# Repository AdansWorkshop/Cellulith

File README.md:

# Cellulith
An RP2040 based IoT/cellular device. Essentially a cell phone but very bulky.

# Why it's called "Cellulith"
Lith means rock or stone. For example, the Earths crust is called the lithosphere because it's a sphere of rock.

Cellu comes from cellular, like cellular phone.

The inspiration for the name was Cellulite, which was proposed by the founder of Oak Dev Tech, however I felt that the "lite" suffix made it sound small.

# Specifications
2aH Li-Po battery with USB-C charging

SIM808 GSM/GPS module with sim card socket on the bottom of the board (sim card not included)

RP2040 Cortex M0+ high-performance microcontroller running at 133MHz

8MB QSPI NOR FLASH storage

320x480 Resistive Touchscreen TFT-LCD Display

Himax HM01B0 CMOS Color Imaging Camera

Digital PWM Audio

Haptic Feedback for SMS/Voice Call notifications

# Board Dimensions
3.8" by 2.6" with M3 mounting holes in all 4 corners

# Case Dimensions
4.2" by 3" by 0.95" excluding antenna

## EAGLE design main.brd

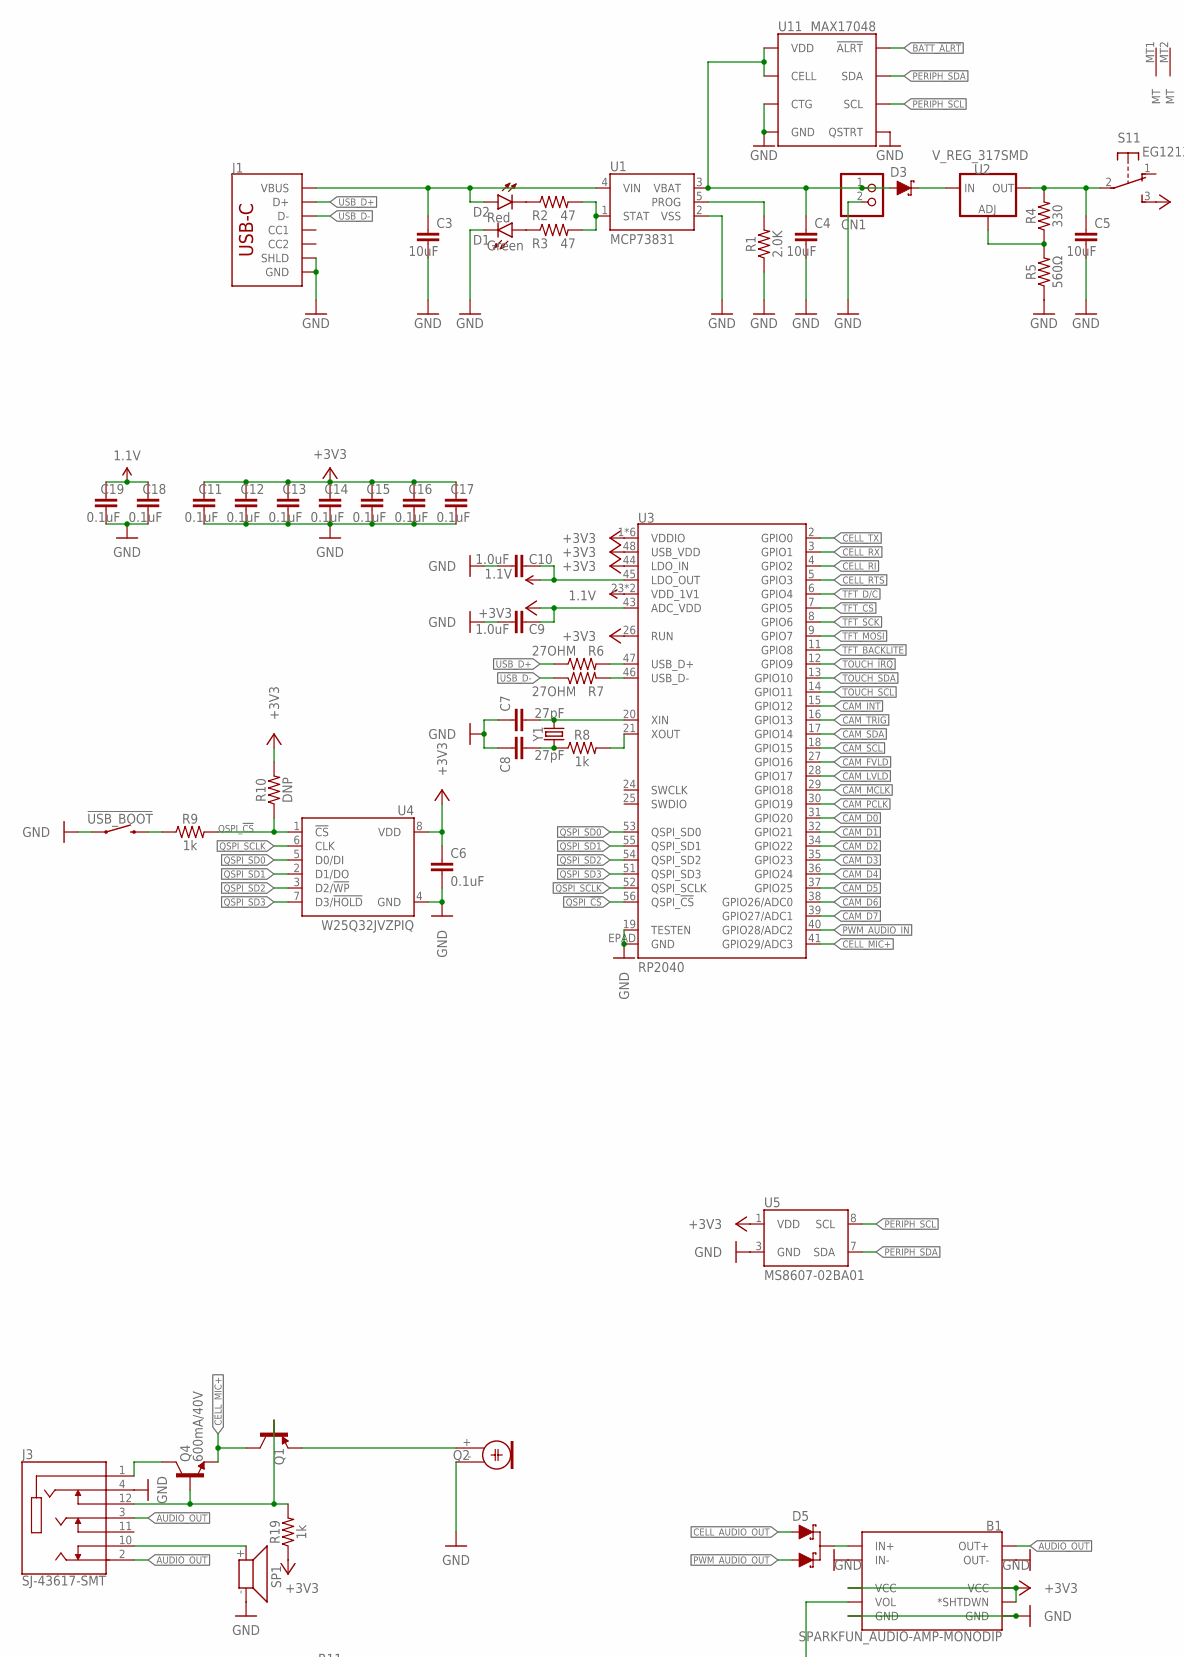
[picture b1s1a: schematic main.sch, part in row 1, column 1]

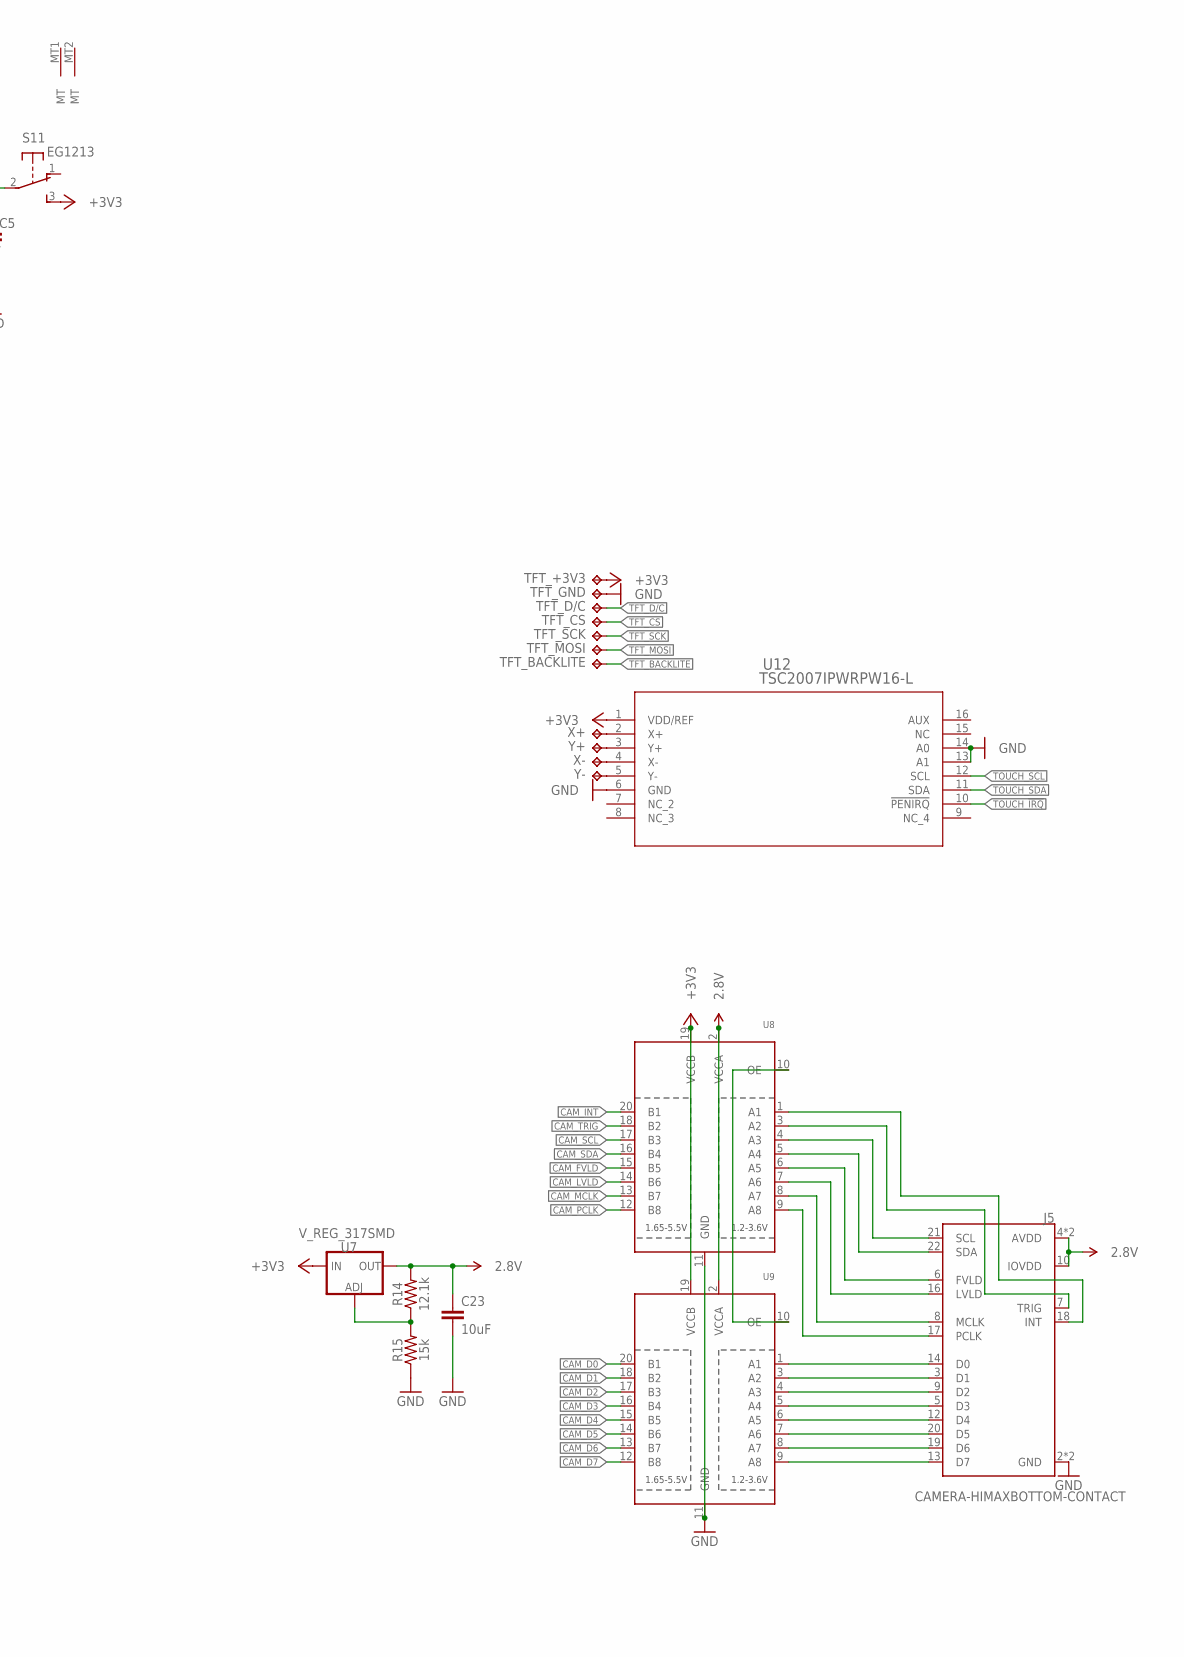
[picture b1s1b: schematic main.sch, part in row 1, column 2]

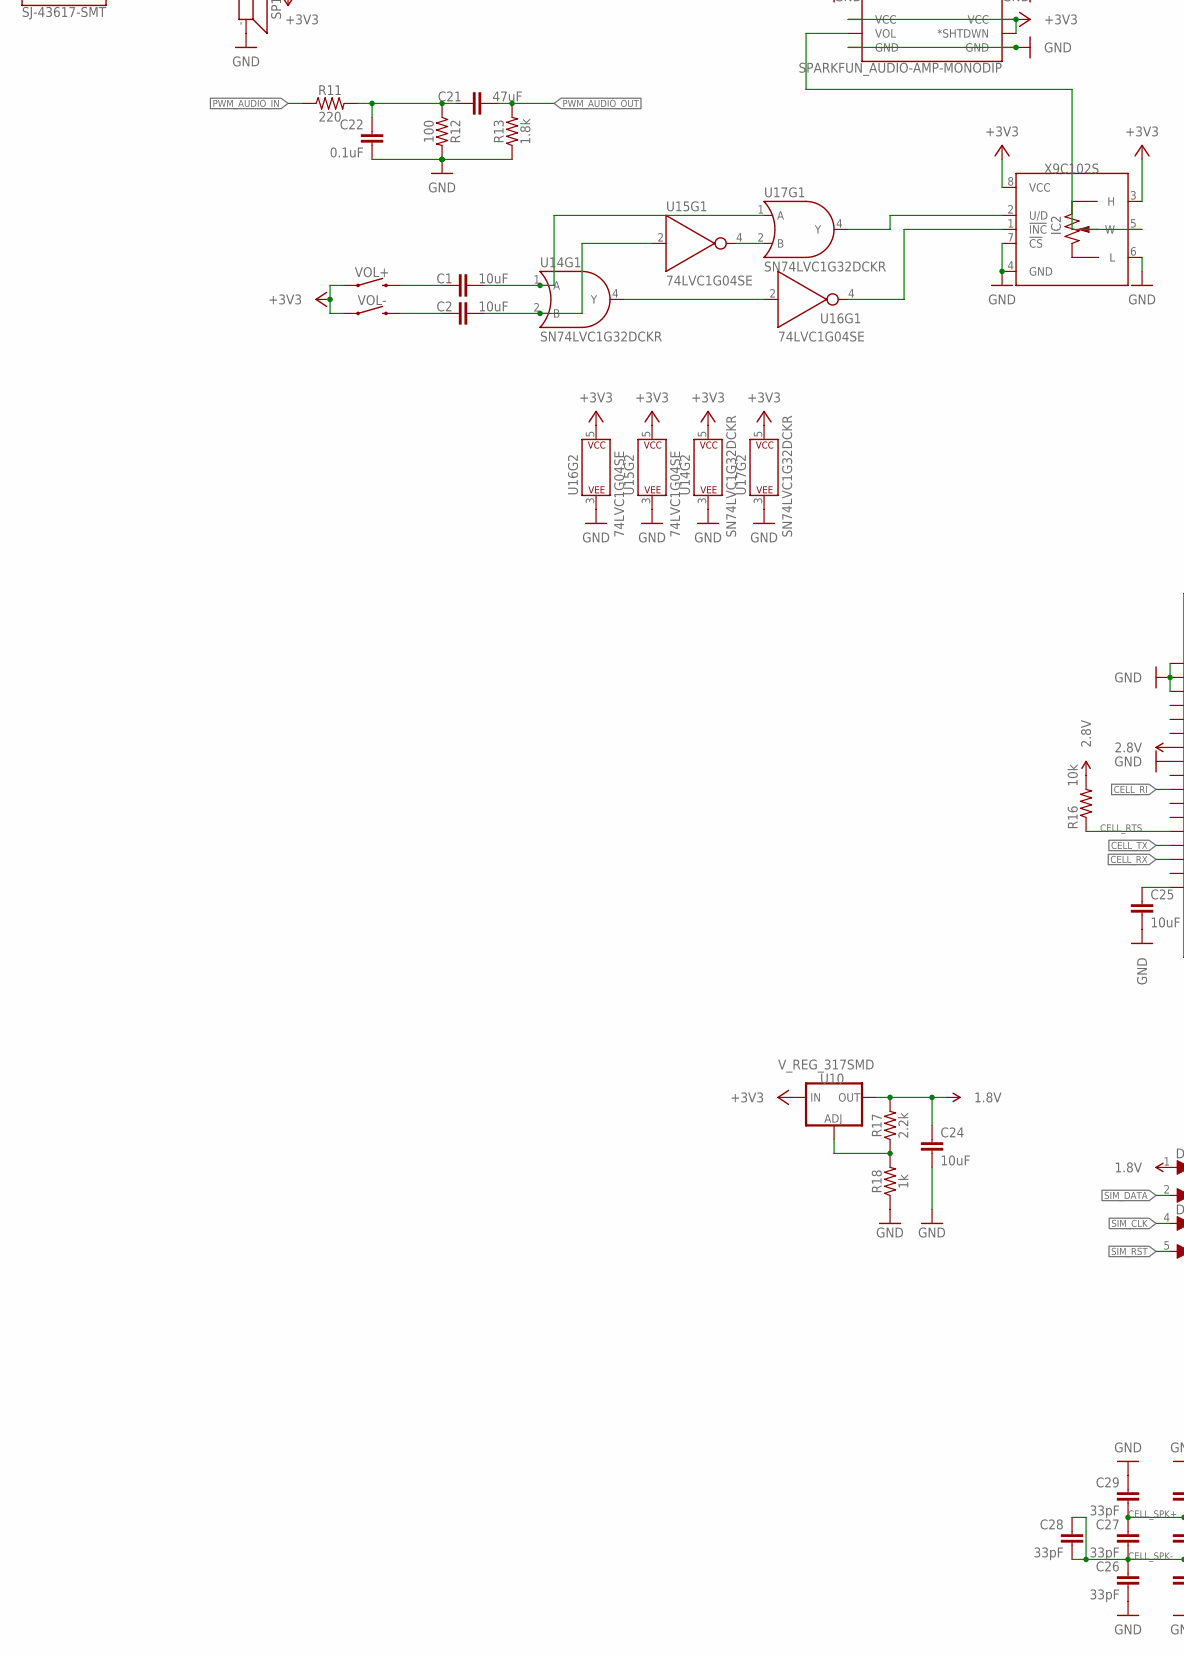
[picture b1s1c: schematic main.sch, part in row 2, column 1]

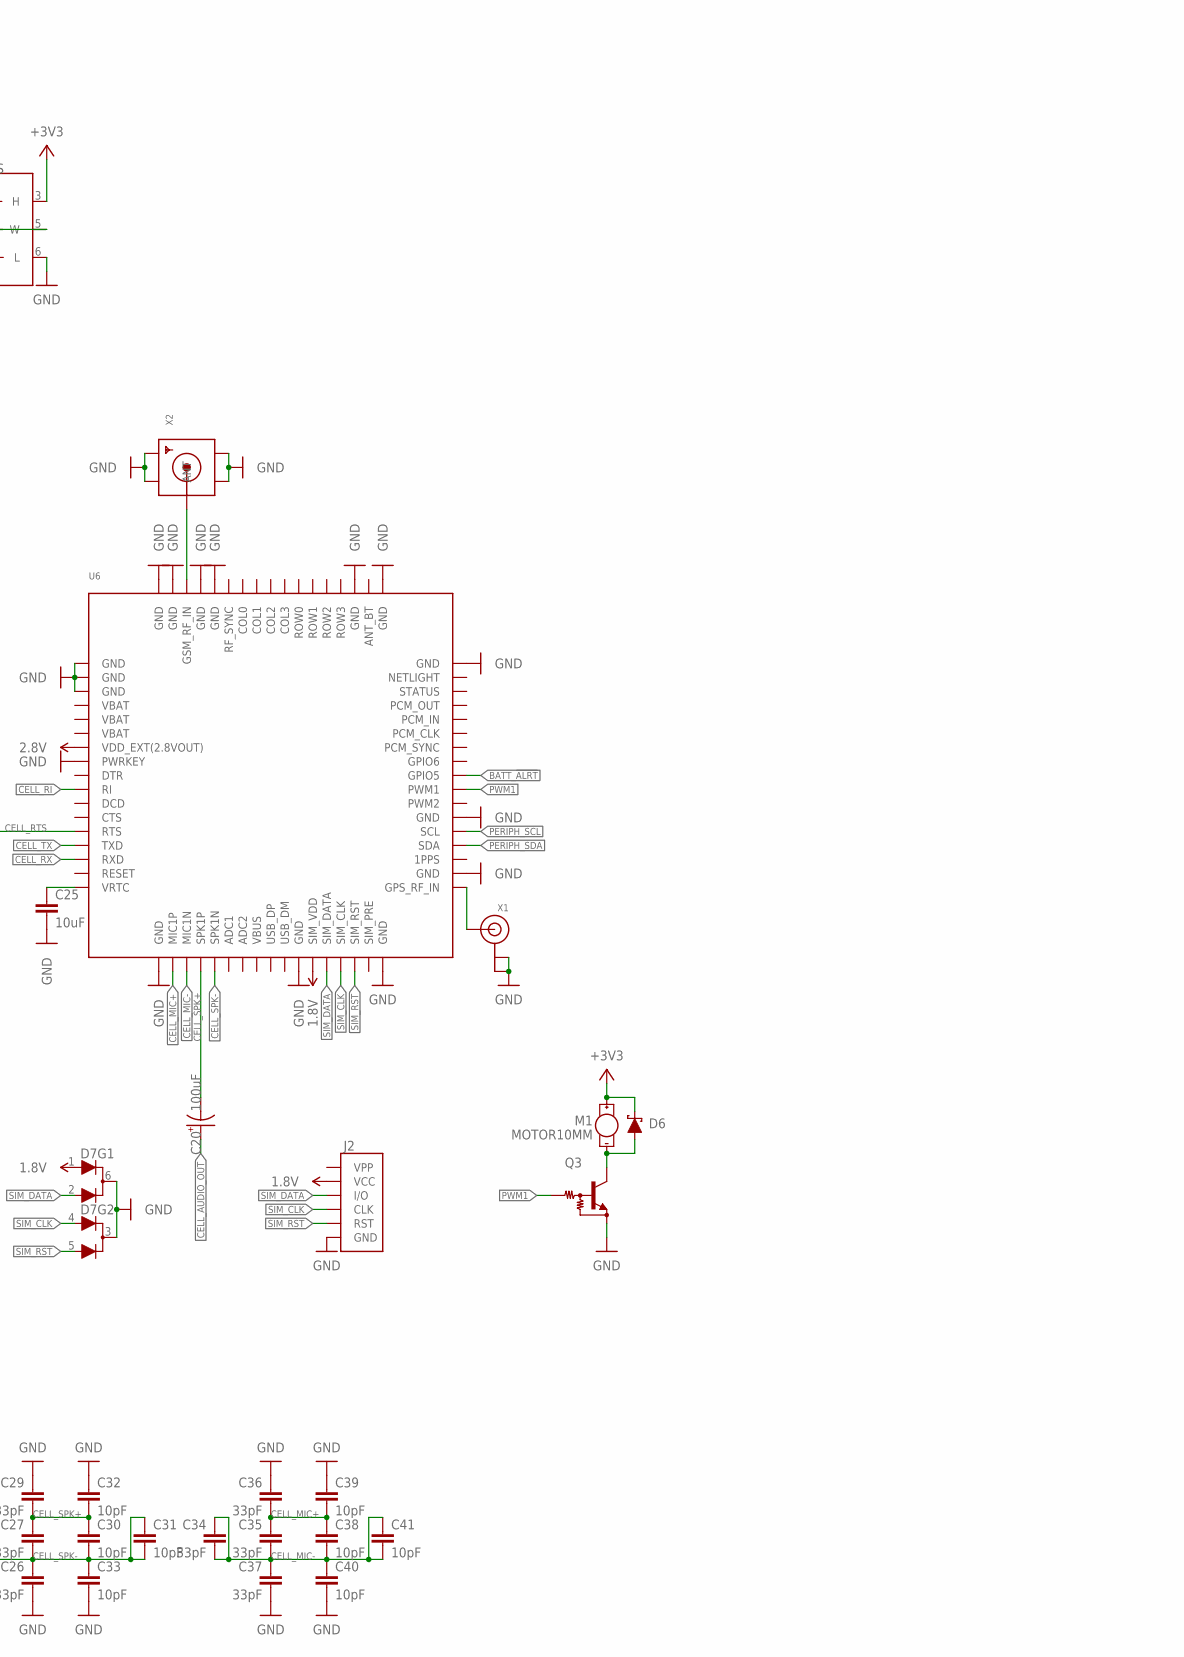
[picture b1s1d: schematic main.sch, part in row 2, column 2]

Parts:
!USB_BOOT: MOMENTARY-SWITCH-SPST-SMD-6.0X3.5MM; TACTILE_SWITCH_SMD_6.0X3.5MM
B1: SPARKFUN_AUDIO-AMP-MONODIP; AUDIO-AMP-MONO
C1, C2, C3, C4, C5, C24: 10uF; 0402-TIGHT
C6, C11, C12, C13, C14, C15, C16, C17, C18, C19, C22: 0.1uF; 0402-TIGHT
C7, C8: 27pF; 0402-TIGHT
C9, C10: 1.0uF; 0402-TIGHT
C20: 100uF; 1206-POLAR
C21: 47uF; 0402-TIGHT
C23, C25: 10uF; 0603
C26, C27, C28, C29, C34, C35, C36, C37: 33pF; 0603
C30, C31, C32, C33, C38, C39, C40, C41: 10pF; 0603
CN1: JST_2PIN-SMT-RA; JST-PH-2-SMT-RA
D1: Green; LED-0603
D2: Red; LED-0603
D3: 3A/10V/280mV; SOD-323
D5: BAS70-05; SOT23-3
D6: 120mA/40V/370mV; SOD-523
D7: BAV70S,115; SOT363
IC2: X9C102S; SOIC08
J1: USB_C_2-LAYER_PADS; USB-C-16P-2LAYER-PADS
J2: SIMHOLDER-SIM; SIMHOLDER
J3: SJ-43617-SMT; CUI_SJ-43617-SMT
J5: CAMERA-HIMAXBOTTOM-CONTACT; FPC-24-AMPHENOL-SFV24R-1STE1HLF
M1: MOTOR10MM; VIBE-MOTOR-10MM
Q1, Q4: 600mA/40V; SOT23-3
Q2: ELECTRET; 9.7ELECTRET
Q3: TRANSISTOR-NPN_MUN2211; TRANSISTOR-NPN_SC59-BEC
R1: 2.0K; 0402-TIGHT
R2, R3: 47; 0402-TIGHT
R4: 330; 0402-TIGHT
R5: 560Ω; 0402-TIGHT
R6, R7: 27OHM; 0402-TIGHT
R8, R9, R18, R19: 1k; 0402-TIGHT
R10: DNP; 0402-TIGHT
R11: 220; 0402-TIGHT
R12: 100; 0402-TIGHT
R13: 1.8k; 0603
R14: 12.1k; 0603
R15: 15k; 0603
R16: 10k; 0402-TIGHT
R17: 2.2k; 0402-TIGHT
S1: EG1213
SP1: SMS-1308MS-2-R
TFT_+3V3: TPTP10R; TP10R
TFT_BACKLITE: TPTP10R; TP10R
TFT_CS: TPTP10R; TP10R
TFT_D/C: TPTP10R; TP10R
TFT_GND: TPTP10R; TP10R
TFT_MOSI: TPTP10R; TP10R
TFT_SCK: TPTP10R; TP10R
U1: MCP73831; SOT23-5
U2, U7, U10: V_REG_317SMD; SOT223
U3: RP2040; QFN-56
U4: W25Q32JVZPIQ; WSON-8-6X5
U5: MS8607-02BA01
U6: GSM_SIM808_LITERAL; SIM900_SMT
U8, U9: TXB0108PWR; TSSOP20
U11: MAX17048; DFN-8
U12: TSC2007IPWRPW16-L; PW16-L
U14, U17: SN74LVC1G32DCKR; SOT353
U15, U16: 74LVC1G04SE; SOT353
VOL+: MOMENTARY-SWITCH-SPST-PTH-RIGHT-ANGLE-8-020; TACTILE_SWITCH_PTH_RA_8-020
VOL-: MOMENTARY-SWITCH-SPST-PTH-RIGHT-ANGLE-8-020; TACTILE_SWITCH_PTH_RA_8-020
X1: ANTENNA_U.FL; U.FL
X2: SMACONNECTOR_EDGE; SMA_EDGELAUNCH
X+: TPTP10R; TP10R
X-: TPTP10R; TP10R
Y1: CRYSTAL-12MHZ; CRYSTAL-SMD-2X2.5MM
Y+: TPTP10R; TP10R
Y-: TPTP10R; TP10R

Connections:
1.1V: C10.1, C18.1, C19.1, U3.23 (VDD_1V1), U3.45 (LDO_OUT), U3.50 (VDD_1V1)
1.8V: C24.1, D7.1 (A1), J2.C1 (VCC), R17.2, U6.P$29 (SIM_VDD), U10.2 (OUT)
2.8V: C23.1, J5.4 (AVDD), J5.10 (IOVDD), J5.11 (AVDD), R14.2, R16.2, U6.P$7 (VDD_EXT(2.8VOUT)), U7.2 (OUT), U8.2 (VCCA), U9.2 (VCCA)
+3V3: B1.PWR+ (VCC), B1.S (*SHTDWN), B1.VOL+ (VCC), C6.1, C9.1, C11.1, C12.1, C13.1, C14.1, C15.1, C16.1, C17.1, D6.C, IC2.3 (H), IC2.8 (VCC), M1.+, R10.2, R19.1, S1.3 (S), TFT_+3V3.TP, U3.1 (VDDIO), U3.10 (VDDIO), U3.22 (VDDIO), U3.26 (RUN), U3.33 (VDDIO), U3.42 (VDDIO), U3.43 (ADC_VDD), U3.44 (LDO_IN), U3.48 (USB_VDD), U3.49 (VDDIO), U4.8 (VDD), U5.1 (VDD), U7.3 (IN), U8.19 (VCCB), U9.19 (VCCB), U10.3 (IN), U12.1 (VDD/REF), U14.5 (P$V+), U15.5 (P$V+), U16.5 (P$V+), U17.5 (P$V+), VOL+.1, VOL-.1
AUDIO_OUT: B1.OUT+, J3.2, J3.3
BATT_!ALRT: U6.P$43 (GPIO5), U11.5 (!ALRT)
CAM_D0: U3.31 (GPIO20), U9.20 (B1)
CAM_D1: U3.32 (GPIO21), U9.18 (B2)
CAM_D2: U3.34 (GPIO22), U9.17 (B3)
CAM_D3: U3.35 (GPIO23), U9.16 (B4)
CAM_D4: U3.36 (GPIO24), U9.15 (B5)
CAM_D5: U3.37 (GPIO25), U9.14 (B6)
CAM_D6: U3.38 (GPIO26/ADC0), U9.13 (B7)
CAM_D7: U3.39 (GPIO27/ADC1), U9.12 (B8)
CAM_FVLD: U3.27 (GPIO16), U8.15 (B5)
CAM_INT: U3.15 (GPIO12), U8.20 (B1)
CAM_LVLD: U3.28 (GPIO17), U8.14 (B6)
CAM_MCLK: U3.29 (GPIO18), U8.13 (B7)
CAM_PCLK: U3.30 (GPIO19), U8.12 (B8)
CAM_SCL: U3.18 (GPIO15), U8.17 (B3)
CAM_SDA: U3.17 (GPIO14), U8.16 (B4)
CAM_TRIG: U3.16 (GPIO13), U8.18 (B2)
CELL_AUDIO_OUT: C20.1 (+), D5.1 (A)
CELL_MIC+: C35.1, C36.2, C38.1, C39.2, Q1.3 (C), Q4.2 (E), U3.41 (GPIO29/ADC3), U6.P$19 (MIC1P)
CELL_MIC-: C34.1, C34.2, C35.2, C37.1, C38.2, C40.1, C41.1, C41.2, U6.P$20 (MIC1N)
CELL_RI: U3.4 (GPIO2), U6.P$10 (RI)
CELL_RTS: R16.1, U3.5 (GPIO3), U6.P$13 (RTS)
CELL_RX: U3.3 (GPIO1), U6.P$15 (RXD)
CELL_SPK+: C20.2 (-), C27.1, C29.2, C30.1, C32.2, U6.P$21 (SPK1P)
CELL_SPK-: C26.1, C27.2, C28.1, C28.2, C30.2, C31.1, C31.2, C33.1, U6.P$22 (SPK1N)
CELL_TX: U3.2 (GPIO0), U6.P$14 (TXD)
GND: !USB_BOOT.1, B1.IN-, B1.OUT-, B1.PWR- (GND), B1.VOL- (GND), C3.2, C4.2, C5.2, C6.2, C7.1, C8.1, C9.2, C10.2, C11.2, C12.2, C13.2, C14.2, C15.2, C16.2, C17.2, C18.2, C19.2, C22.2, C23.2, C24.2, C25.2, C26.2, C29.1, C32.1, C33.2, C36.1, C37.2, C39.1, C40.2, CN1.2 (1), D1.C, D7.3 (C), D7.6 (C), IC2.4 (GND), IC2.6 (L), IC2.7 (!CS), J1.GND, J1.GND2 (GND), J1.SHLD1 (SHLD), J1.SHLD2 (SHLD), J1.SHLD3 (SHLD), J1.SHLD4 (SHLD), J2.C5 (GND), J3.4, J5.2 (GND), J5.15 (GND), Q2.- (1), Q3.E, R1.1, R5.1, R12.2, R13.1, R15.1, R18.1, SP1.- (2), TFT_GND.TP, U1.2 (VSS), U3.19 (TESTEN), U3.EPAD (GND), U4.4 (GND), U5.3 (GND), U6.P$1 (GND), U6.P$2 (GND), U6.P$3 (GND), U6.P$8 (PWRKEY), U6.P$18 (GND), U6.P$28 (GND), U6.P$34 (GND), U6.P$36 (GND), U6.P$40 (GND), U6.P$51 (GND), U6.P$52 (GND), U6.P$54 (GND), U6.P$64 (GND), U6.P$65 (GND), U6.P$67 (GND), U6.P$68 (GND), U8.11 (GND), U9.11 (GND), U11.1 (CTG), U11.4 (GND), U11.6 (QSTRT), U11.9 (GND), U12.6 (GND), U12.13 (A1), U12.14 (A0), U14.3 (P$V-), U15.3 (P$V-), U16.3 (P$V-), U17.3 (P$V-), X1.1 (GND), X1.2 (GND), X2.GND@1 (GND4), X2.GND@2 (GND3), X2.GND@3 (GND2), X2.GND@4 (GND1)
unnamed: C5.1, R4.2, S1.2, U2.2 (OUT)
unnamed: C1.2, U14.1 (A), U17.1 (A)
unnamed: C2.2, U14.2 (B), U15.2 (A)
unnamed: C3.1, D2.A, J1.VBUS1 (VBUS), J1.VBUS2 (VBUS), U1.4 (VIN)
unnamed: R2.2, R3.2, U1.1 (STAT)
unnamed: D2.C, R2.1
unnamed: D1.A, R3.1
unnamed: R1.2, U1.5 (PROG)
unnamed: U15.4 (Y), U17.2 (B)
unnamed: D3.C, U2.3 (IN)
unnamed: R4.1, R5.2, U2.1 (ADJ)
unnamed: C1.1, VOL+.2
unnamed: U14.4 (Y), U16.2 (A)
unnamed: R6.2, U3.47 (USB_D+)
unnamed: R7.2, U3.46 (USB_D-)
unnamed: R8.2, U3.21 (XOUT)
unnamed: C7.2, U3.20 (XIN), Y1.P3 (2)
unnamed: C8.2, R8.1, Y1.P1 (1)
unnamed: !USB_BOOT.2, R9.1
unnamed: J5.14 (D0), U9.1 (A1)
unnamed: J5.3 (D1), U9.3 (A2)
unnamed: J3.10, SP1.+ (1)
unnamed: C21.1, C22.1, R11.2, R12.1
unnamed: B1.IN+, D5.3 (C)
unnamed: R14.1, R15.2, U7.1 (ADJ)
unnamed: J5.9 (D2), U9.4 (A3)
unnamed: U8.10 (OE), U9.10 (OE)
unnamed: J5.5 (D3), U9.5 (A4)
unnamed: J5.20 (D5), U9.7 (A6)
unnamed: J5.12 (D4), U9.6 (A5)
unnamed: J5.19 (D6), U9.8 (A7)
unnamed: J5.13 (D7), U9.9 (A8)
unnamed: J5.17 (PCLK), U8.9 (A8)
unnamed: J5.8 (MCLK), U8.8 (A7)
unnamed: J5.16 (LVLD), U8.7 (A6)
unnamed: J5.6 (FVLD), U8.6 (A5)
unnamed: J5.22 (SDA), U8.5 (A4)
unnamed: J5.21 (SCL), U8.4 (A3)
unnamed: J5.7 (TRIG), U8.3 (A2)
unnamed: J5.18 (INT), U8.1 (A1)
unnamed: U6.P$35 (GPS_RF_IN), X1.3 (SIGNAL)
unnamed: D6.A, M1.-, Q3.C
unnamed: C4.1, CN1.1 (2), D3.A, U1.3 (VBAT), U11.2 (CELL), U11.3 (VDD)
unnamed: IC2.2 (U/D), U17.4 (Y)
unnamed: U6.P$66 (GSM_RF_IN), X2.P (ANT)
unnamed: R17.1, R18.2, U10.1 (ADJ)
unnamed: C25.1, U6.P$17 (VRTC)
unnamed: Q1.2 (E), Q2.+ (2)
unnamed: IC2.1 (!INC), U16.4 (Y)
unnamed: C2.1, VOL-.2
unnamed: B1.VOL, IC2.5 (W)
unnamed: U12.2 (X+), X+.TP
unnamed: U12.3 (Y+), Y+.TP
unnamed: U12.4 (X-), X-.TP
unnamed: U12.5 (Y-), Y-.TP
unnamed: J3.12, Q1.1 (B), Q4.1 (B), R19.2
unnamed: J3.1, Q4.3 (C)
PERIPH_SCL: U5.8 (SCL), U6.P$39 (SCL), U11.7 (SCL)
PERIPH_SDA: U5.7 (SDA), U6.P$38 (SDA), U11.8 (SDA)
PWM1: Q3.B, U6.P$42 (PWM1)
PWM_AUDIO_IN: R11.1, U3.40 (GPIO28/ADC2)
PWM_AUDIO_OUT: C21.2, D5.2 (A1), R13.2
QSPI_!CS: R9.2, R10.1, U3.56 (QSPI_!CS!), U4.1 (!CS!)
QSPI_SCLK: U3.52 (QSPI_SCLK), U4.6 (CLK)
QSPI_SD0: U3.53 (QSPI_SD0), U4.5 (D0/DI)
QSPI_SD1: U3.55 (QSPI_SD1), U4.2 (D1/DO)
QSPI_SD2: U3.54 (QSPI_SD2), U4.3 (D2/!WP!)
QSPI_SD3: U3.51 (QSPI_SD3), U4.7 (D3/!HOLD!)
SIM_CLK: D7.4 (A1), J2.C3 (CLK), U6.P$31 (SIM_CLK)
SIM_DATA: D7.2 (A2), J2.C7 (I/O), U6.P$30 (SIM_DATA)
SIM_RST: D7.5 (A2), J2.C2 (RST), U6.P$32 (SIM_RST)
TFT_BACKLITE: TFT_BACKLITE.TP, U3.11 (GPIO8)
TFT_CS: TFT_CS.TP, U3.7 (GPIO5)
TFT_D/C: TFT_D/C.TP, U3.6 (GPIO4)
TFT_MOSI: TFT_MOSI.TP, U3.9 (GPIO7)
TFT_SCK: TFT_SCK.TP, U3.8 (GPIO6)
TOUCH_!IRQ: U3.12 (GPIO9), U12.10 (!PENIRQ)
TOUCH_SCL: U3.14 (GPIO11), U12.12 (SCL)
TOUCH_SDA: U3.13 (GPIO10), U12.11 (SDA)
USB_D+: J1.A6 (D+), J1.B6 (D+), R6.1
USB_D-: J1.A7 (D-), J1.B7 (D-), R7.1
VBAT: U6.P$4 (VBAT), U6.P$5 (VBAT), U6.P$6 (VBAT)
VBUS: U6.P$25 (VBUS)

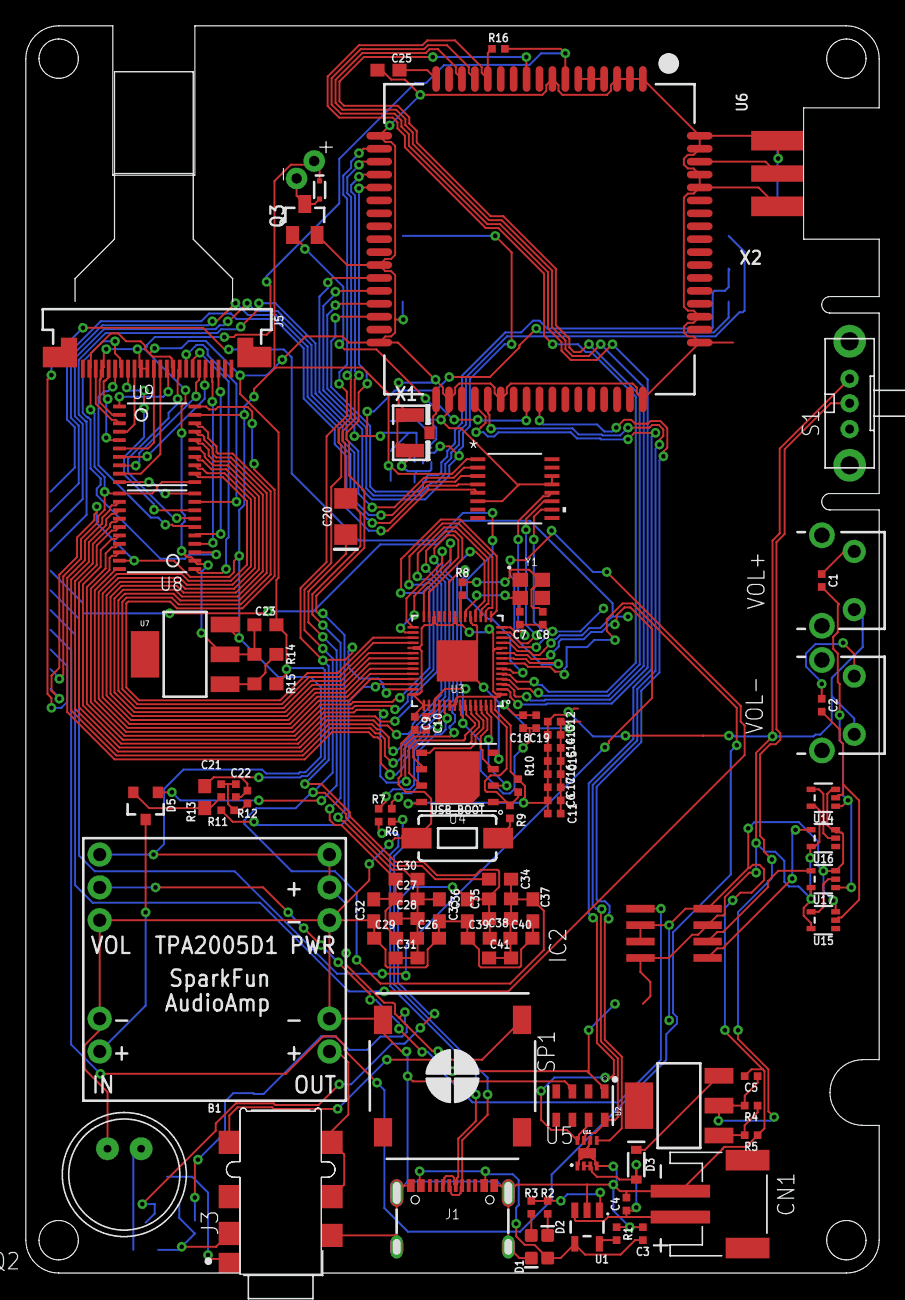
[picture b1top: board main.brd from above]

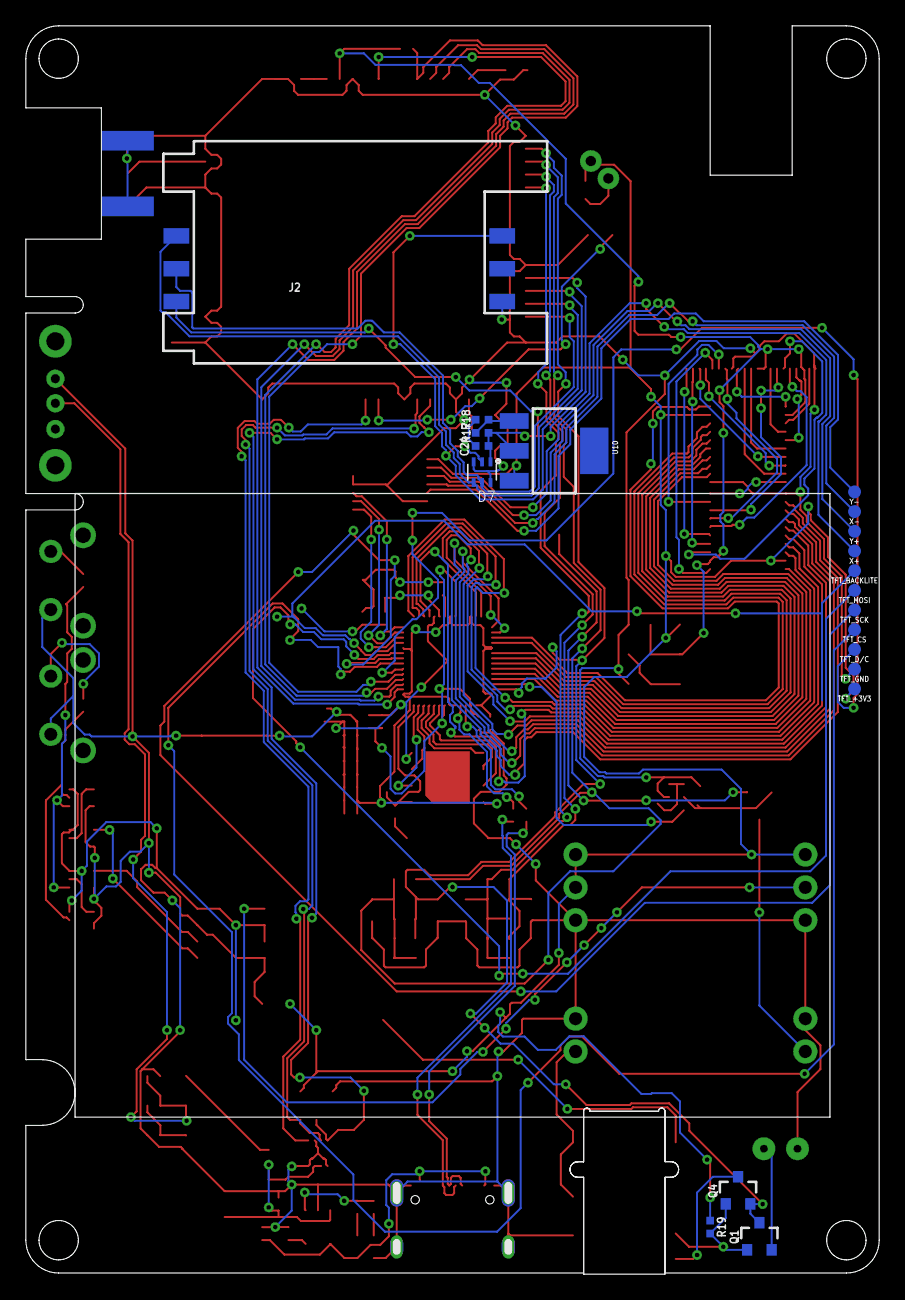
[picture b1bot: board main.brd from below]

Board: 2 copper layers, 66.0 x 96.6 mm, 113 parts (20 on the bottom side), 114 nets.

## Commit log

2023-03-30 EAGLE project files
2023-03-30 Case STEP files
2023-03-30 Organized schematic
2023-03-30 Added Case STEP files
2023-03-31 Charset
    each character is 10*20 pixels. the grid is 26*4. each character can be represented by a single byte. column{00000)(000}row
2023-03-31 removed charset background
    each character is 10*20 pixels. the grid is 26*4. each character can be represented by a single byte. column{00000)(000}row
2023-04-05 Create m
2023-04-05 Added Cellulith Programs directory and BearCraft

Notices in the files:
parts and their libraries:
SparkFun-Connectors: Licensing: Creative Commons ShareAlike 4.0 International - https://creativecommons.org/licenses/by-sa/4.0
COPYRIGHT: Copyright (C) 2023 Ultra Librarian. All rights reserved.
